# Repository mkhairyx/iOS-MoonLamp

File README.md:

# iOS Moon Lamp

Bought a battery powered Moon lamp a few years ago, and it was cool back then but now it’s boring that I have to turn it on and off manually every night. So I removed the insides of it and made it powered with an ESP32 controlled by the iOS Home app.

## The Poster

High resolution poster available [here](./Media/Pictures/PSD/MoonLamp.png).

## The Design

### The PCB:
Here's how the PCB looks like:

And here's the gerber view for it:

### The Schematics:

### The case:
The case is held together with four M5 screws.

## Assembly
### Step Files

Check [Step_Files](./Step_Files/) to see step files.

### Exploded View:

### Assembly video:
This video shows how to assemble and disassemble the case:

https://github.com/user-attachments/assets/3fa87b10-48f1-4240-b7dd-df9781dbfde8

## Firmware
### Compile and flash using the Arduino IDE
If you want to edit the code, compile it yourself, then flash it; you can download the arduino sketch and the required libraries [here](./source/Software/Arduino).
### Flash the firmware as is
If you want to flash the firmware as is, you can download it [here](./source/Software/Firmware). <br>
You can use [ESPWebTool](https://esptool.spacehuhn.com) to flash the firmware directly to the ESP32 using your browser.

## Operating the device
### Power
The device is powered by a USB-C and does not have a battery, so please make sure that it's connected to a stable USB-C power source. 
The device shows wether it's powered on or not through the Red LED on the back near the USB-C port.

### Blue Status LED
The device shows it's status through the Blue Status LED on the back near the USB-C port. 
Refer to [HomeSpan's documentation on HomeSpan Device Status](https://github.com/HomeSpan/HomeSpan/blob/master/docs/UserGuide.md#homespan-device-status) to be able to identify different states.

### CLI
The CLI can be used to setup the device, change the WI-FI credentials, or factory reset the system.[^cli]
You can use the CLI through the onboard USB-C port on the back. Use a baud rate of 9600 for serial communication.

### Control Button
The Control Button can be used to put the device in Command Mode and select different actions.
Refer to [HomeSpan's documentation on Device Command Mode](https://github.com/HomeSpan/HomeSpan/blob/master/docs/UserGuide.md#device-command-mode) to know how to use it

## BOM
Available as a .csv file [here](./BOM/BOM.csv)
### BOM Table (components only)
(Pricing for the enclosure and the PCB will depend on where the stuff are made)
|Name             |Value         |Link                                                                                                        |Cost (EGP) per one|Cost (USD)|Total Cost (EGP)|Total Cost (USD)      |Qty                   |Description           |
|-----------------|--------------|------------------------------------------------------------------------------------------------------------|------------------|----------|----------------|----------------------|----------------------|----------------------|
|Capacitor        |22uF          |https://lampatronics.com/product/smd-multilayer-ceramic-capacitor-1210-22uf-16v-1pcs                        | EGP 2.00         | $0.038   | EGP 6.00       | $0.12                |3                     |                      |
|Capacitor        |100nf         |https://lampatronics.com/product/smd-multilayer-ceramic-capacitor-1206-100nf-50v-1pcs                       | EGP 1.50         | $0.029   | EGP 10.50      | $0.03                |7                     |                      |
|Capacitor        |4.7uF         |https://lampatronics.com/product/smd-multilayer-ceramic-capacitor-1206-4-7uf-16v-1pcs                       | EGP 1.50         | $0.029   | EGP 1.50       | $0.03                |1                     |                      |
|Main LED         |WS2812B LED   |https://uge-one.com/product/f5-5mm-ws2812b-rgb-smart-led-5v/                                                | EGP 17.10        | $0.329   | EGP 17.10      | $0.33                |1                     |                      |
|Power LED        |RED LED       |https://lampatronics.com/product/smd-led-0603-red-10pcs                                                     | EGP 6.00         | $0.115   | EGP 6.00       | $0.12                |1                     |                      |
|Status LED       |BLUE LED      |https://lampatronics.com/product/smd-led-0603-blue-10pcs                                                    | EGP 6.00         | $0.115   | EGP 6.00       | $0.12                |1                     |                      |
|USB-C            |16P           |https://www.ram-e-shop.com/shop/usb9-c-type-pcb-usb-connector-on-pcb-c-type-type-female-16-pin-sku-usb9-8125| EGP 5.00         | $0.096   | EGP 5.00       | $0.10                |1                     |                      |
|Resistor         |5.1k ohm      |https://lampatronics.com/product/resistor-5-1k-ohm-1-4w-2pcs                                                | EGP 0.30         | $0.006   | EGP 0.30       | $0.01                |1                     |1 pack of 2 resistors |
|Resistor         |2k            |https://lampatronics.com/product/smd-resistor-2kohm-202-0805-10pcs                                          | EGP 2.00         | $0.038   | EGP 2.00       | $0.04                |1                     |1 pack of 10 resistors|
|Resistor         |22k           |https://lampatronics.com/product/smd-resistor-22kohm-223-0805-10pcs                                         | EGP 2.00         | $0.038   | EGP 2.00       | $0.04                |1                     |1 pack of 10 resistors|
|Resistor         |47k           |https://lampatronics.com/product/smd-resistor-47k-473-ohm-0805-10pcs                                        | EGP 2.00         | $0.038   | EGP 2.00       | $0.04                |1                     |1 pack of 10 resistors|
|Resistor         |10k           |https://lampatronics.com/product/smd-resistor-10kohm-103-0805-10pcs                                         | EGP 2.00         | $0.038   | EGP 2.00       | $0.04                |1                     |1 pack of 10 resistors|
|Resistor         |220           |https://lampatronics.com/product/smd-resistor-220ohm-221-0805-10pcs                                         | EGP 2.00         | $0.038   | EGP 2.00       | $0.04                |1                     |1 pack of 10 resistors|
|Switch           |              |https://lampatronics.com/product/push-button-long-right-angle-2pin2base-7x7-5x6mm                           | EGP 1.50         | $0.029   | EGP 3.00       | $0.03                |2                     |Boot and Enable       |
|Switch           |              |https://lampatronics.com/product/push-button-4pin-long-6x6x13mm                                             | EGP 1.50         | $0.029   | EGP 1.50       | $0.03                |1                     |Control               |
|Voltage Regulator|AMS1117-3.3   |https://lampatronics.com/product/ams1117-adj-sot-223-adj-linear-voltage-regulator                           | EGP 2.00         | $0.038   | EGP 2.00       | $0.04                |1                     |                      |
|Programmer chip  |CP2102N       |https://uge-one.com/product/cp2102-gmr-usb-to-uart-bridge-controller-qfn-28/                                | EGP 250.00       | $4.810   | EGP 250.00     | $4.81                |1                     |                      |
|Main MCU         |ESP32-WROOM-32|https://uge-one.com/product/espressif-esp32-wroom-32-dual-core-wi-fi-bluetooth-iot-module/                  | EGP 290.00       | $5.579   | EGP 290.00     | $5.58                |1                     |                      |
|Optocoupler      |PC817         |https://www.ram-e-shop.com/shop/pc817-pc817-el817c-f-5866                                                   | EGP 2.00         | $0.038   | EGP 2.00       | $0.04                |1                     |                      |
|Touch sensor     |TTP223        |https://lampatronics.com/product/ttp223-touch-button-module                                                 | EGP 10.00        | $0.192   | EGP 10.00      | $0.19                |1                     |                      |
|                 |              |                                                                                                            |                  |          |                |                      |                      |                      |
|                 |              |                                                                                                            |                  |          | EGP 620.90     | $11.74               |                      |                      |

### Orders from different manufacturers
#### In Egypt:
[Nori](norisolutions.com) (PCB only): $19.05

[metanoia](metanoia-eg.com) (Case only): $5.77

#### Out of Egypt (international shipping): 
[JLCPCB](https://jlcpcb.com/) (both PCB and Case): $32.42

## Notes
The TTP 223 module is connected to the main PCB using three wires. <br>
The 3D printed case, the PCB, and the Moon itself (the lamp) are not included in the BOM, but their costs are shown in [Orders from different manufacturers](./#Orders-from-different-manufacturers).
The Moon Lamp it self was salvaged from an old lamp, so it costs nothing, therefore it wasn't included in the BOM.

> Made and designed by [@mkhairyx](https://github.com/mkhairyx).<br>
Supported by [Fallout](https://fallout.hackclub.com/) and [Hack Club](https://hackclub.com).<br>
Powered by [HomeSpan](https://github.com/HomeSpan/HomeSpan)<br>
<hr>

[^cli]: Check the [The HomeSpan Command-Line Interface (CLI)](https://github.com/HomeSpan/HomeSpan/blob/master/docs/CLI.md) to be able to use the device's CLI through the onboard USB-C port.

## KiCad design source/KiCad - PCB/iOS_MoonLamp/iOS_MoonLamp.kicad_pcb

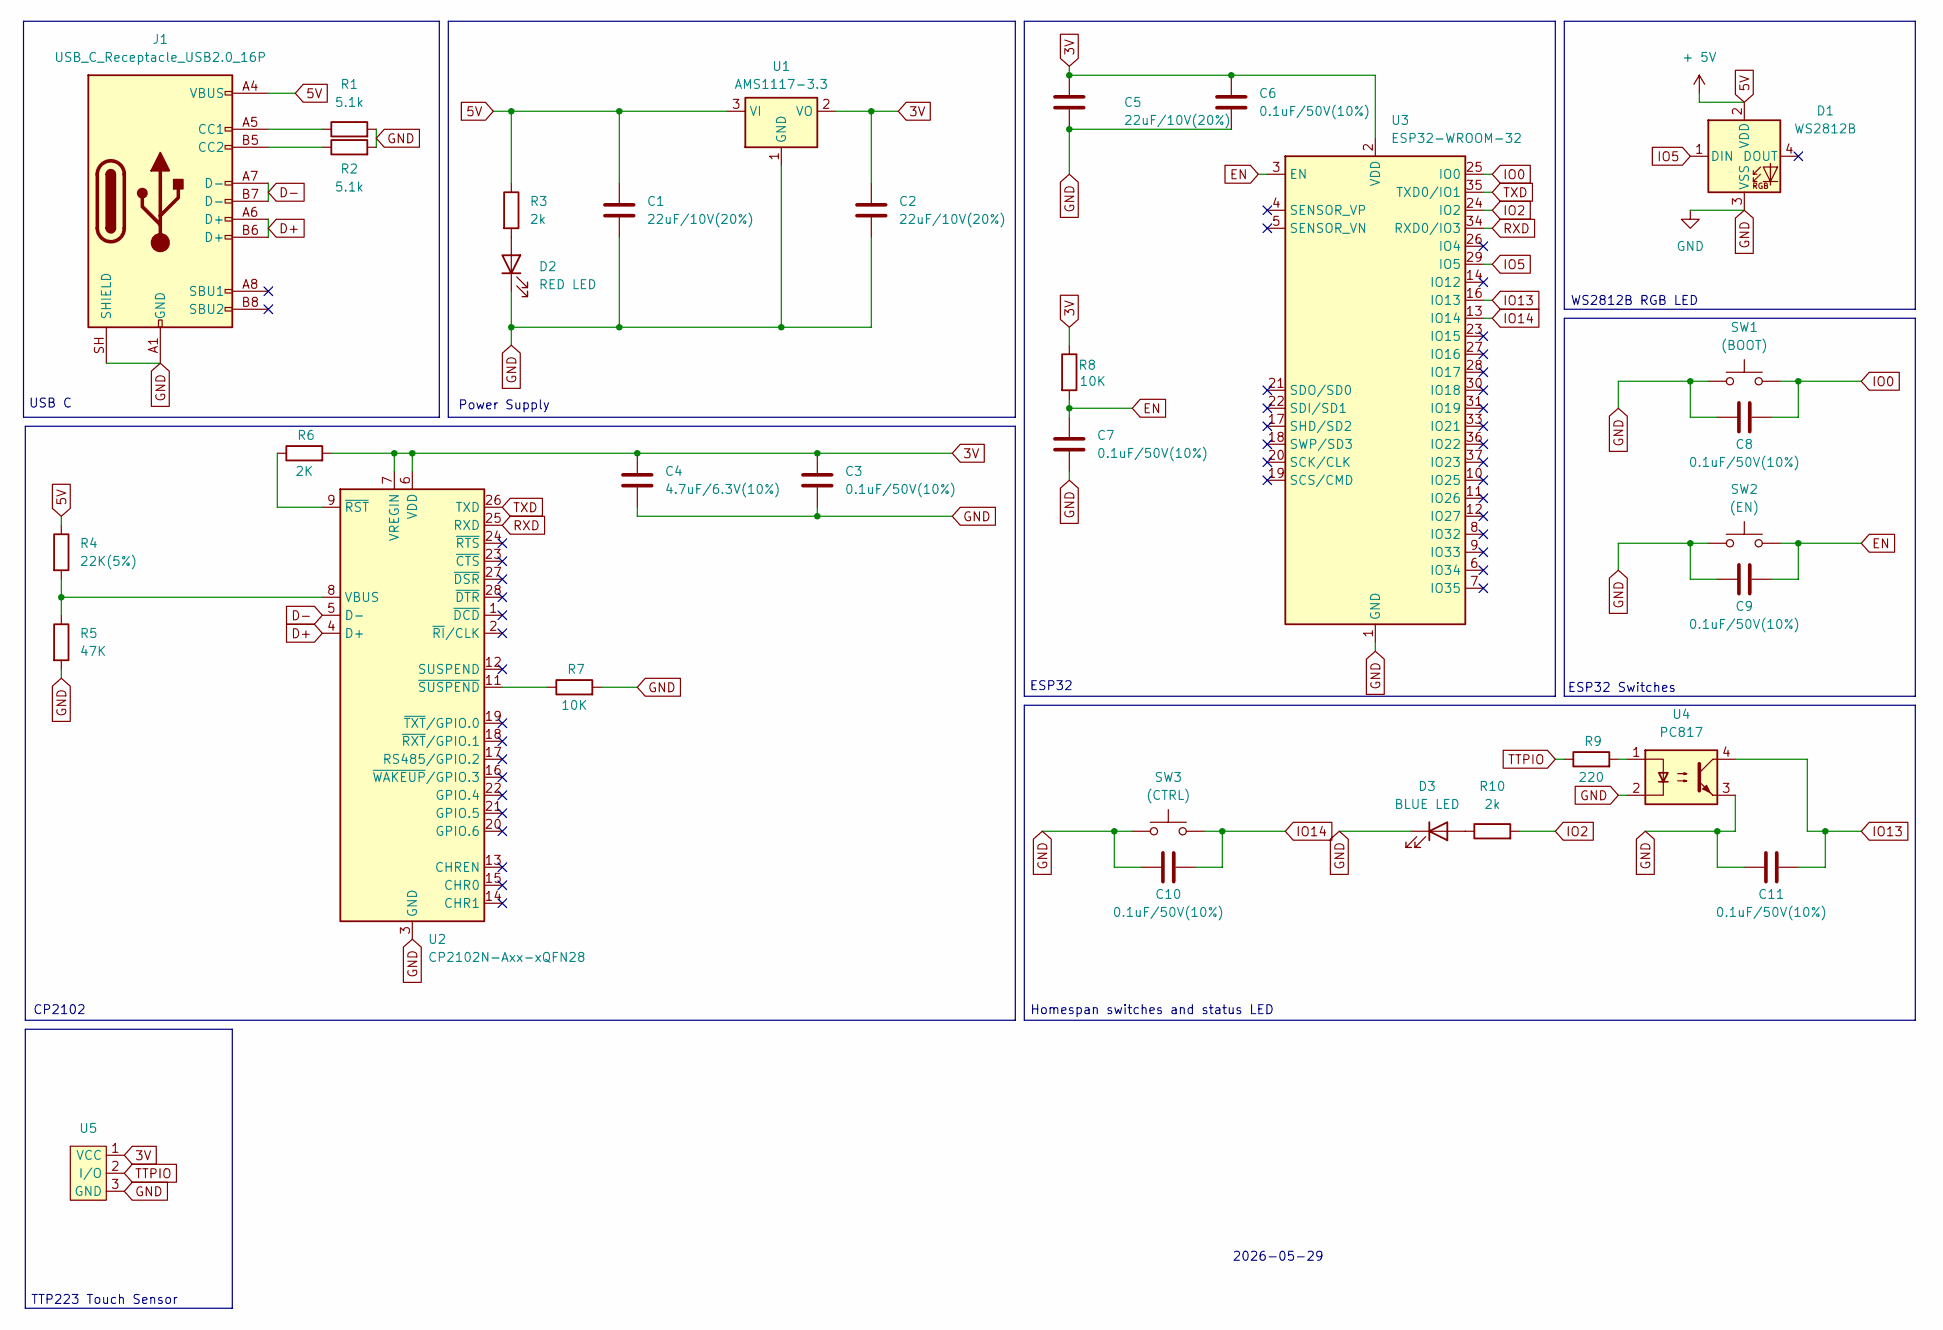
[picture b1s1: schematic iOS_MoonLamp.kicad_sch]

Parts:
C1, C2, C5: 22uF/10V(20%); C_1210_3225Metric_Pad1.33x2.70mm_HandSolder
C3, C6, C7, C8, C9, C10, C11: 0.1uF/50V(10%); C_1206_3216Metric_Pad1.33x1.80mm_HandSolder
C4: 4.7uF/6.3V(10%); C_1206_3216Metric_Pad1.33x1.80mm_HandSolder
D1: WS2812B; LED_D5.0mm-4_RGB_Wide_Pins
D2: RED LED; LED_0603_1608Metric_Pad1.05x0.95mm_HandSolder
D3: BLUE LED; LED_0603_1608Metric_Pad1.05x0.95mm_HandSolder
J1: USB_C_Receptacle_USB2.0_16P; USB_C_Receptacle_GCT_USB4105-xx-A_16P_TopMnt_Horizontal
R1, R2: 5.1k; R_Axial_DIN0207_L6.3mm_D2.5mm_P7.62mm_Horizontal
R3, R10: 2k; R_0805_2012Metric_Pad1.20x1.40mm_HandSolder
R4: 22K(5%); R_0805_2012Metric_Pad1.20x1.40mm_HandSolder
R5: 47K; R_0805_2012Metric_Pad1.20x1.40mm_HandSolder
R6: 2K; R_0805_2012Metric_Pad1.20x1.40mm_HandSolder
R7, R8: 10K; R_0805_2012Metric_Pad1.20x1.40mm_HandSolder
R9: 220; R_0805_2012Metric_Pad1.20x1.40mm_HandSolder
SW1: (BOOT); SW_Tactile_SPST_Angled_PTS645Vx58-2LFS
SW2: (EN); SW_Tactile_SPST_Angled_PTS645Vx58-2LFS
SW3: (CTRL); SW_PUSH_6mm_H13mm
U1: AMS1117-3.3; SOT-223-3_TabPin2
U2: CP2102N-Axx-xQFN28; QFN-28-1EP_5x5mm_P0.5mm_EP3.35x3.35mm
U3: ESP32-WROOM-32
U4: PC817; DIP-4_W7.62mm
U5: Untitled

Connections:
3V: C2.1, C3.1, C4.1, C5.1, C6.1, R6.2, R8.1, U1.2 (VO), U2.6 (VDD), U2.7 (VREGIN), U3.2 (VDD), U5.1 (VCC)
5V: C1.1, D1.2 (VDD), J1.A4 (VBUS), J1.A9 (VBUS), J1.B4 (VBUS), J1.B9 (VBUS), R3.1, R4.1, U1.3 (VI)
D+: J1.A6 (D+), J1.B6 (D+), U2.4 (D+)
D-: J1.A7 (D-), J1.B7 (D-), U2.5 (D-)
EN: C7.1, C9.2, R8.2, SW2.2, U3.3 (EN)
GND: C1.2, C2.2, C3.2, C4.2, C5.2, C6.2, C7.2, C8.1, C9.1, C10.1, C11.1, D1.3 (VSS), D2.1 (K), D3.1 (K), J1.A1 (GND), J1.A12 (GND), J1.B1 (GND), J1.B12 (GND), J1.SH (SHIELD), R1.2, R2.2, R5.2, R7.2, SW1.1, SW2.1, SW3.1, U1.1 (GND), U2.3 (GND), U2.29 (GND), U3.1 (GND), U3.15 (GND), U3.38 (GND), U3.39 (GND), U4.2, U4.3, U5.3 (GND)
IO0: C8.2, SW1.2, U3.25 (IO0)
IO2: R10.2, U3.24 (IO2)
IO5: D1.1 (DIN), U3.29 (IO5)
IO13: C11.2, U3.16 (IO13), U4.4
IO14: C10.2, SW3.2, U3.13 (IO14)
unnamed: D2.2 (A), R3.2
unnamed: D3.2 (A), R10.1
unnamed: J1.A5 (CC1), R1.1
unnamed: J1.B5 (CC2), R2.1
unnamed: R9.2, U4.1
unnamed: R4.2, R5.1, U2.8 (VBUS)
unnamed: R6.1, U2.9 (~RST)
unnamed: R7.1, U2.11 (~SUSPEND)
RXD: U2.25 (RXD), U3.34 (RXD0/IO3)
TTPIO: R9.1, U5.2 (I/O)
TXD: U2.26 (TXD), U3.35 (TXD0/IO1)

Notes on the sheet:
Power Supply
TTP223 Touch Sensor
ESP32 Switches
USB C
CP2102
ESP32
Homespan switches and status LED
2026-05-29
WS2812B RGB LED

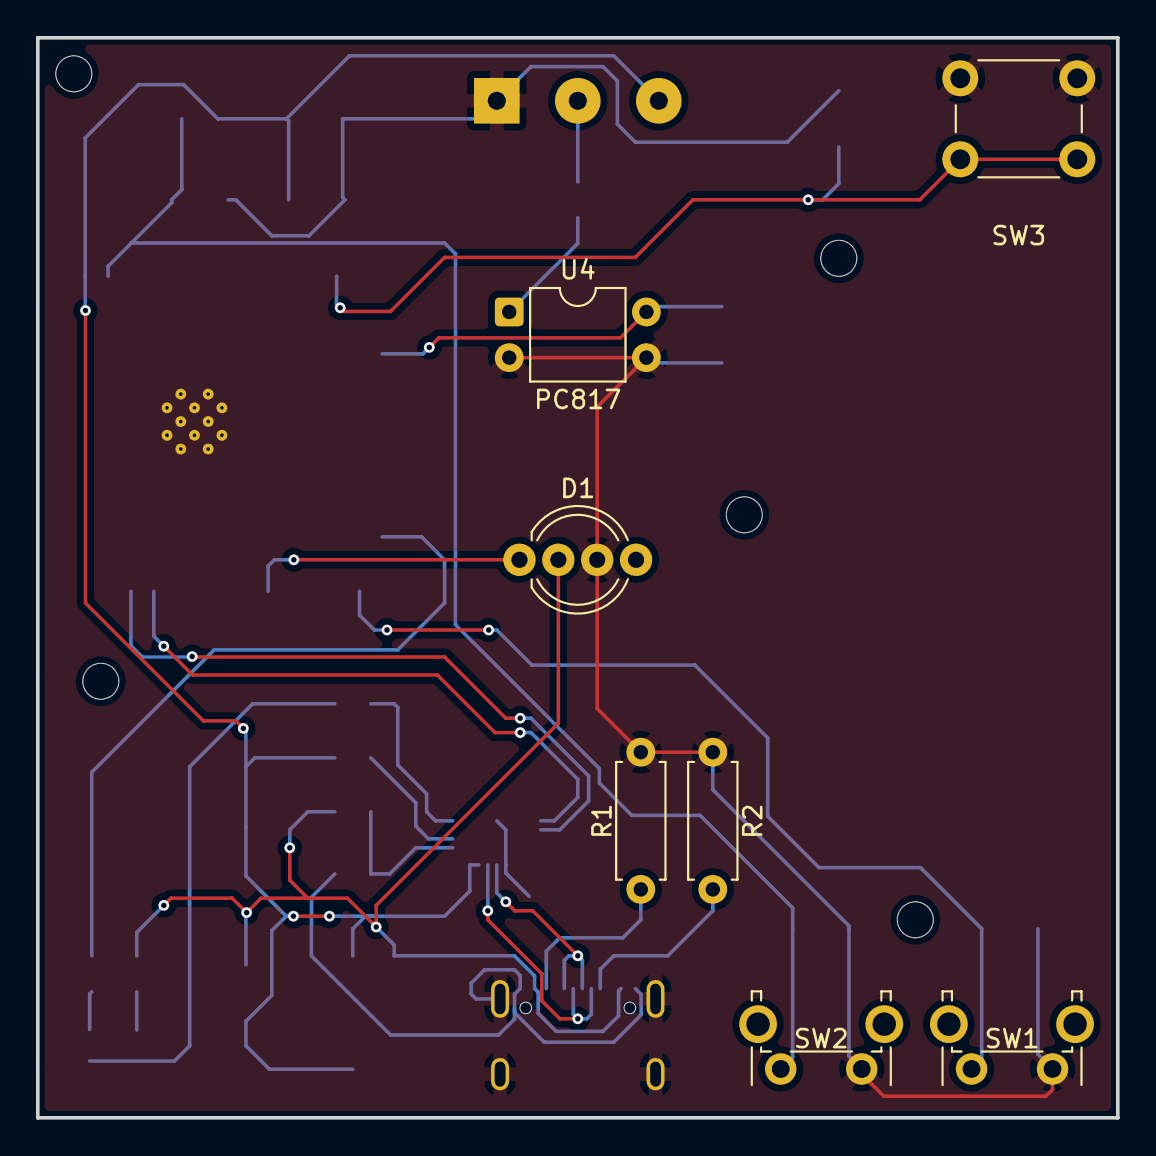
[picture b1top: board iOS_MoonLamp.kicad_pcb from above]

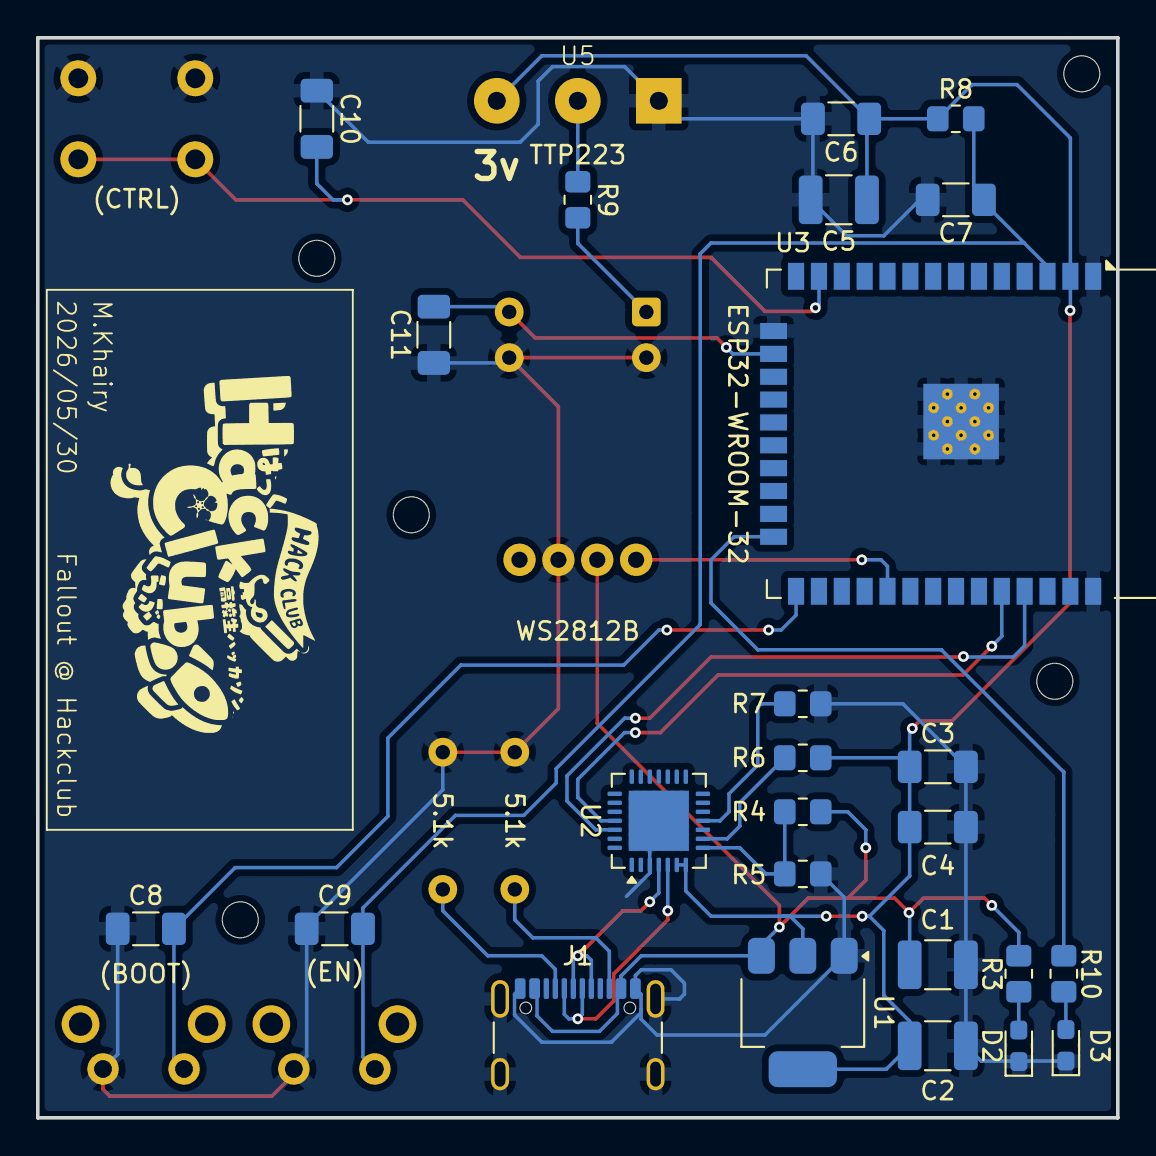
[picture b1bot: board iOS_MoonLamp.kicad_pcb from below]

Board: 2 copper layers, 60.0 x 60.0 mm, 33 parts (26 on the bottom side), 22 nets.

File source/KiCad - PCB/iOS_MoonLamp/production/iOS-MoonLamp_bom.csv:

Designator,Footprint,Quantity,Value,LCSC Part #
"C1, C2, C5",1210,3,22uF/10V(20%),
"C10, C11, C3, C6, C7, C8, C9",1206,7,0.1uF/50V(10%),
C4,1206,1,4.7uF/6.3V(10%),
D1,LED_D5.0mm-4_RGB_Wide_Pins,1,WS2812B,
D2,0603,1,RED LED,
D3,0603,1,BLUE LED,
J1,USB_C_Receptacle_GCT_USB4105-xx-A_16P_TopMnt_Horizontal,1,USB_C_Receptacle_USB2.0_16P,
"R1, R2",R_Axial_DIN0207_L6.3mm_D2.5mm_P7.62mm_Horizontal,2,5.1k,
"R10, R3, R6",0805,3,2k,
R4,0805,1,22K(5%),
R5,0805,1,47K,
"R7, R8",0805,2,10K,
R9,0805,1,220,
SW1,SW_Tactile_SPST_Angled_PTS645Vx58-2LFS,1,(BOOT),
SW2,SW_Tactile_SPST_Angled_PTS645Vx58-2LFS,1,(EN),
SW3,SW_PUSH_6mm_H13mm,1,(CTRL),
U1,SOT-223-3_TabPin2,1,AMS1117-3.3,
U2,QFN-28-1EP_5x5mm_P0.5mm_EP3.35x3.35mm,1,CP2102N-Axx-xQFN28,
U3,ESP32-WROOM-32,1,ESP32-WROOM-32,
U4,DIP-4_W7.62mm,1,PC817,
U5,Untitled,1,~,

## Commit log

2026-06-04 .\BOM\
2026-06-04 adding bom
2026-06-04 adding excalidraw diagrams
2026-06-04 adding pictures
2026-06-04 adding media pictures
2026-06-04 Create Media folder
2026-06-04 Making folders for pictures
2026-06-04 adding media
2026-06-04 rename video
2026-06-04 adding kicad source files
2026-06-04 adding source fusion 3d files
2026-06-04 uploading software
2026-06-04 renaming files and deleting temp files
2026-06-04 Rename iOS Moon Light v12.png to iOS_MoonLamp.png
2026-06-04 Adding camera folder and camera pic for the Moon Lamp.
2026-06-04 mp4 version of the assembly video
2026-06-04 Create README.md for iOS Moon Lamp project
    Added detailed project information, including design, assembly instructions, and bill of materials.
2026-06-04 Fix formatting issues in README.md
2026-06-04 Update README with operating instructions for the device
    Added sections on device operation, including power, status LED, CLI, and control button usage.
2026-06-05 Update README with case assembly details
2026-06-07 Adding the Poster and some pics for the moonlamp.
2026-06-07 Added low res poster for faster loading
2026-06-07 Update README with poster
2026-06-07 Added a link for high res poster
2026-06-07 Added zine.pdf
2026-06-07 Add notes section to README
2026-06-07 added zine png
2026-06-07 Fix formatting in TTP 223 module notes
2026-06-07 Update README with firmware instructions
2026-06-08 Added production files
2026-06-08 Enhance README with BOM and manufacturer order details
    Added BOM table and orders from different manufacturers sections to README.
2026-06-08 Added costs for the case through metanoia
2026-06-11 Deleted autorouting files (note to reviewers: I attempted auto routing and failed at it. I routed everything manual but forgot to continue recording. I'll be rerouting everything manually and record 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
2026-06-11 Rerouted the PCB
2026-06-11 Added a Prices in usd column for the BOM
2026-06-11 Clean up BOM.csv by removing empty lines
    Removed empty lines and adjusted total row formatting.
2026-06-11 Remove empty line in BOM.csv
    Removed empty line from BOM.csv.
2026-06-11 edited BOM to have total cost per component
2026-06-11 Fix BOM.csv
2026-06-11 fix BOM
2026-06-11 fixed prices
2026-06-11 fix prices
2026-06-11 Revise BOM table with pricing details and notes
    Updated BOM table to include pricing per unit and total cost for components. Added notes regarding pricing for enclosure and PCB manufacturing.
2026-06-11 Added step files
2026-06-11 Add step files section to README
    Added a section for step files in the assembly instructions.
2026-06-11 Fixed BOM
2026-06-11 Clean up BOM.csv by removing empty rows
    Removed empty rows from BOM.csv to clean up the data.
2026-06-11 Revise BOM table with total cost calculations
    Updated BOM table to include total costs and improved formatting.
2026-06-12 Update pricing information for manufacturers
